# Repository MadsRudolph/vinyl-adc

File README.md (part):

# Vinyl ADC

[Assembly guide & bench log](https://vinyl-adc.madsrudolph.dev/) · [Rev D bring-up, 20 October](docs/bringup-log-2026-10-rev-d.md) · [Bring-up log, 16–18 September](docs/bringup-log-2026-09.md) · [16 September bench plan](assembly/sessions/2026-09-16/README.md) · [6 September test handoff](assembly/sessions/2026-09-06/README.md)

**Rev D (20 October): built, made by PCBWay, and running.** The converter now lives on one four-layer Raspberry Pi HAT, [fabricated by PCBWay](#rev-d-the-pcbway-board), in place of the four hand-milled boards it was born on. Both channels modulated correctly from the first capture, and with the turntable connected the whole chain records about **8 dB more A-weighted range** than the milled stack did, on the Pi's own 5 V. On the bench, on its own crystal, the left channel measures **78.7 dB dynamic range**, 11 dB past the milled stack's best. Record: [rev D bring-up log](docs/bringup-log-2026-10-rev-d.md).

**The milled stack (September):** all four boards are assembled and bench-screened with the AD3 (16–17 September): power, rev B digital with the on-board crystal Pierce, both channels and the full stack pass, after resoldering a crystal leg and swapping the reference op-amp U2 to an LM358 for output headroom on the charge-pump rail (design-notes §10b′). A Raspberry Pi 4 captures the stream, and a ripper service on it records sides automatically, splits and tags the tracks and hands finished albums to the Jellyfin server; setup in [pi/README.md](pi/README.md) and [server/README.md](server/README.md). No complete-system audio performance is claimed by these assembly tests.

**Rev C (22 September):** with a fab available, the four milled boards are redrawn as [one 4-layer board](hardware/kicad/rev_c/README.md), 170 × 120 mm, all through-hole, with the Raspberry Pi 4 plugged into its underside on its own 40-pin header and the bench fixes (LM358 reference, filtered 5 V inlet, series resistors on the I2S clocks) built in. It passes the same intent gate as the milled boards against the reference sheet; [production files](production/vinyl_adc_rev_c/) and a [bill of materials](docs/bom-rev-c.md) are exported. It was never built: rev D superseded it.

**Rev D (designed 22–25 September):** with PCBWay sponsoring the fabrication, the one-board converter is redrawn as a proper [Raspberry Pi HAT](hardware/kicad/rev_d/README.md) — 140 × 136 mm (its layout redone on 24 September: every passive beside the pin it serves, channel R a copy of channel L), four layers, still every part through-hole from the DTU shop — and given the things the bench asked for: an analog supply island behind its own choke (the DAC reference rail, kept away from the Pi's and the charge pump's switching), a second 74HC244 to stiffen the −5 V pump, a damped MCLK, eight front-edge status LEDs (rail, pump, clock-alive, clip L/R from LM339 window comparators, and three under the Pi's control), shutdown and user buttons, a HAT ID EEPROM, test-point headers with ground pins, and a tonearm ground terminal with a lift network. `tools/check_rev_d.py` proves it is the reference circuit plus exactly those additions; [production files](production/vinyl_adc_rev_d/) and the [bill of materials](docs/bom-rev-d.md) are exported. Design record: [design-notes §12](docs/design-notes.md#12-rev-d-the-converter-as-a-raspberry-pi-hat-22-september-2026).

**Rev E (24 September):** the same circuit in common [surface-mount parts](hardware/kicad/rev_e/README.md) on a 118 × 88 mm four-layer HAT — 0805 C0G/X7R and thin-film parts, SOIC logic and op-amps, SOT-23 transistors, shielded SMD chokes — checked by the same gate as rev D, placed and routed by the same tools, DRC clean. [Production files](production/vinyl_adc_rev_e/) include the pick-and-place file for PCBWay assembly; [bill of materials](docs/bom-rev-e.md); design record [design-notes §13](docs/design-notes.md).

<p align="center">

</p>

<p align="center">
  <strong>A Discrete 3rd-Order Continuous-Time Delta-Sigma Stereo Audio ADC</strong><br>
  Engineered from standard analog op-amps &amp; 74HC CMOS logic — <em>zero dedicated ADC ICs anywhere in the signal chain</em>.<br>
  Now one four-layer Raspberry Pi HAT <strong>made by <a href="https://www.pcbway.com">PCBWay</a></strong>; first built on four boards isolation-milled on a Roland SRM-20 using <a href="https://github.com/MadsRudolph/srm-cam"><strong>SRM-CAM</strong></a>.
</p>

<p align="center">
  <a href="media/showcase/README.md">Download GIF animations &amp; print files</a>
</p>

<details>
<summary><strong>More views: the enclosure orbit and exploded assembly</strong></summary>

### Product orbit

### Exploded assembly

</details>

<p align="center">
  👉 <strong><a href="https://madsrudolph.github.io/vinyl-adc/">Launch Live Interactive 3D Web Viewer &amp; Explosion Slider</a></strong> 👈
</p>

---

## Rev D: the PCBWay board

**One board, four layers, made by [PCBWay](https://www.pcbway.com), and the best-measuring version of this converter so far.**

Every Vinyl ADC board before rev D was isolation-milled, single-sided, at the university workshop. When **PCBWay offered to sponsor the fabrication**, the converter could finally be drawn the way a mixed-signal circuit wants to be: one board, a solid ground plane, plated holes everywhere, and the Raspberry Pi plugged in underneath. Thank you to PCBWay for making that possible; this section is about what their boards did for the project.

<p align="center">
  <br>
  <sub>Before and after: the four-board milled stack, and rev D as PCBWay made it.</sub>
</p>

<p align="center">
  
  <br>
  <sub>The bare board as it arrived, both sides.</sub>
</p>

### What PCBWay made

| | Rev D, per board |
|---|---|
| Stack-up | **4 layers**: signals / solid GND plane / split +5V·+5VA / signals, 1.6 mm FR-4, 1 oz copper |
| Finish | green solder mask on both sides, white silkscreen, HASL lead-free |
| Holes | **636 plated through-holes and 13 vias**: 649 plated barrels on every board, five boards |
| Routing | 1,020 tracks, the narrowest 0.25 mm; drills from 0.4 mm to 2.7 mm |
| Legends | 184 reference designators at 1 mm text height, the smallest labels 0.8 mm |
| Parts | 184, every one through-hole, socketed ICs |
| Size | 140 × 136 mm, a Raspberry Pi 4 HAT |

<p align="center">
  
  <br>
  <sub>Up close: legends under a millimetre tall come out clean, and every barrel is plated and tinned.</sub>
</p>

### Ordering and what arrived

These are the first professionally made boards I have ever had, so I was very excited to get my hands on them. The order went in through PCBWay's normal online flow on 25 September, from the Gerbers with the copper layer order in the remarks, and their engineers had no questions for me. That was shortly before China's National Day holiday, so things took a little longer, which is understandable and no problem at all. The boards were built up and running on my bench by 20 October.

The package felt premium: the boards were vacuum-sealed in bubble wrap and cushioned by soft styrofoam, which made unpacking them a pleasure. I found no issues with their quality. Assembling them, every footprint matched its part exactly, the clear silkscreen made placing the components easy, and the pre-tinned HASL pads were very nice to hand-solder.

I have built one board so far, since one is all the project needs, so the others are untested spares. On the one I built, no fault has traced back to the fab.

### Why a fab board, for a converter

- **A real ground plane.** A delta-sigma modulator switches at 1.536 MHz next to integrators that resolve microvolts. On one milled layer, ground was whatever copper was left between tracks. On rev D an entire inner layer is ground, directly under every signal, and a large part of the improvement measured below is owed to it.
- **Plated holes.** Every joint is soldered from one side and the barrel carries it through. The single most expensive fault of the September bring-up, a −5 V rail that reached one board only through solder wicked up an unplated hole, cannot exist on this board.
- **Repeatability.** Five identical boards. The milled boards were each a one-off; a second rev D is the same board as the first.

### Milled against fabricated

| | Milled stack (Sept 2026) | Rev D by PCBWay (Oct 2026) |
|---|---|---|
| Boards | 4 × 100 × 100 mm, stacked on a bus | **1 × 140 × 136 mm** Raspberry Pi HAT |
| Copper | 1 layer, milled, bare copper | **4 layers** with a solid ground plane |
| Links | dozens of wire jumpers | **none**: plated through-holes and vias |
| Finish | none | solder mask both sides, silkscreen, HASL lead-free |
| Supply for best figures | bench supply (the Pi's 5 V cost 6–11 dB) | **the Pi's 5 V**, analog island behind its own choke |
| Bring-up | two days, two hidden faults in one channel | **both channels healthy and matched at the first capture** |

**Measured, with the turntable connected** (stylus up, same phono stage, same method, music peaks set to −6 dBFS on both builds):

| 20 Hz–20 kHz | Milled stack, bench supply, crystal clock | **Rev D, Pi 5 V, Pi clock** (crystal not yet running) |
|---|---|---|
| Idle floor, A-weighted | −61.1 / −62.1 dBFS | **−69.7 / −68.2 dBFS** |
| Idle floor, 200 Hz–2 kHz | −68.6 / −69.4 dBFS | **−73.7 / −73.6 dBFS** |
| Idle floor, 2–20 kHz | −59.6 / −60.6 dBFS | **−76.5 / −70.5 dBFS** |
| Music peak to floor, A-weighted | 54.2 / 55.2 dB | **63.7 / 62.2 dB** |
| Music peak to floor, unweighted | 48.9 / 49.2 dB | **51.4 / 51.3 dB** |

### What that adds up to

About **8 dB more A-weighted range** from the groove to the file, and a noise floor 5–17 dB lower everywhere above 200 Hz, measured on the Raspberry Pi's 5 V (the supply that cost the milled stack the most) and, at the time, on the Pi's own clock. What remains in the unweighted figure is 50 Hz hum common to both channels: the turntable's grounding, not the converter.

**On the bench, with its own crystal** (AD3 generator into the input, other input shorted, Pi supply):

| | Milled stack, best channel | **Rev D, left** | Rev D, right |
|---|---|---|---|
| Dynamic range (AES17, A-weighted) | 67.9 dB | **78.7 dB** | 72.2 dB |
| THD at −6 dBFS | 0.03 % | **0.019 %** | 0.052 % |
| Crosstalk | −92.4 dB | **−97.8 dB** | −85.8 dB |
| Response 20 Hz–16 kHz | ±0.06 dB | −0.30 / +0.08 dB | −0.33 / +0.08 dB |

The left channel is **about 11 dB better than anything the milled boards achieved**, and 10 dB past the ~68 dB the design was simulated for. The right channel carries an extra in-band floor that the milled stack's right channel had too; it is traced to the right modulator's own loop and still being chased ([bring-up log §10](docs/bringup-log-2026-10-rev-d.md#10-the-right-channels-deficit-is-in-its-loop-and-it-is-not-new)).

Bring-up said as much as the measurements. The milled stack took two days and two faults that hid each other before its right channel modulated. On rev D both channels were healthy, and matched, on the first capture. The one rev D fault found so far is my own design error, not the fab's: the clip-LED comparators' inputs are swapped in the schematic, documented as an [erratum](docs/bringup-log-2026-10-rev-d.md#7-erratum-the-clip-leds-are-lit-all-the-time) with a rework that stays on the underside.

<p align="center">
  <br>
  <sub>Assembled and running on its Raspberry Pi 4.</sub>
</p>

<p align="center">
  <br>
  <sub>CAD renders (<a href="media/showcase/rev-d/README.md">all views and how they are made</a>); Raspberry Pi 4 model from the FreeCAD parts library, CC BY 3.0.</sub>
</p>

The [Gerbers and production files](production/vinyl_adc_rev_d/), the [KiCad project](hardware/kicad/rev_d/README.md) and the [full rev D bring-up log](docs/bringup-log-2026-10-rev-d.md) are all in this repo. Boards sponsored by **[PCBWay](https://www.pcbway.com)**: thank you for making the project's best version possible.

---

## Audiophile Engineering Specifications

| Specification | Target / Measured Performance | Design Rationale & Implementation |
|---|---|---|
| **Modulator Topology** | Continuous-Time CIFB (Cascade of Integrators, Feedback) | 3rd-order active RC loop with local resonator feedback (`G = 0.03`) |
| **Dynamic Range / SNR** | **Rev D: 78.7 dB left, 72.2 dB right** (AES17, A-weighted). Milled stack: 67.9 dB, best channel | Purposefully matched to the physical vinyl surface noise floor (~60–65 dB) |
| **Audio Output** | **24-bit / 48 kHz Linear PCM FLAC** | Decimated in software on Raspberry Pi CPU (CIC filter + compensation FIR) |
| **Modulator Sampling Rate ($F_s$)** | **1.536 MHz** ($32\times$ OverSampling Ratio) | Matches bandwidth constraints of DTU-stocked op-amps (`TL072` 3 MHz GBW) |
| **Master Clock ($F_{clk}$)** | **6.144 MHz crystal Pierce oscillator** (74HCU04 + HC-49 crystal) | Direct low-jitter clock ($<50\text{ ps}$ jitter vs. Pi PLL phase noise); also available as a plug-in module for the rev A board |
| **Digital Stream Format** | Bit-Interleaved PDM on standard I2S bus | 3.072 Mbps data stream, read as 32-bit stereo audio frames at 48 kHz |
| **Analog Inputs** | Gold RCA Phono Jacks &amp; 5.08 mm Screw Terminals | Switchable input gain via front-panel multi-turn trim potentiometer |
| **Analog Grounding** | Star-ground topology with tonearm binding post | Eliminates 50 Hz turntable motor hum and ground-loop switching transients |
| **PCB Manufacturing** | Rev D: 4-layer 1.6 mm FR-4, HASL lead-free, by **[PCBWay](https://www.pcbway.com)**. First build: isolation-milled single-sided FR4 | Milled toolpaths generated via [**SRM-CAM**](https://github.com/MadsRudolph/srm-cam) on a **Roland SRM-20** mill |
| **Enclosure Dimensions** | $144.0\text{ mm} \times 144.0\text{ mm} \times 105.0\text{ mm}$ | Open organic lattice, reinforced connector islands and M3 lid inserts; recessed $3.0\text{ mm}$ acrylic lid |

---

## Printable enclosure

The enclosure has an open, rounded lattice on all four sides and 40 mm more height for the PCB stack and cable routing. Solid connector islands and reinforced lid-insert bosses carry the mounting loads. **Print upright with supports**; the revised mesh and supported slice pass validation, but physical print/fit testing is still pending.

[STL, 3MF, insert-fit coupon and printing instructions](enclosure/README.md) · [Three looping GIFs](media/showcase/README.md)

## Signal Processing Flow

```
   ┌─────────────────────────────────────────────────────────────────────────────┐
   │                          ANALOG SIGNAL CHAIN (HARDWARE)                     │
   │                                                                             │
   │  Turntable (Debut Carbon)                                                  │
   │         │                                                                   │
   │         ▼                                                                   │
   │  Phono Preamplifier                                                         │
   │         │                                                                   │
   │         ▼                                                                   │
   │  [ VINYL ADC ] ──> 3rd-Order CT-ΔΣ ──> 1.536 MHz PDM ──> 74HC157 Mux       │
   │   Gold RCA In      TL072 + LM311       74HC74 Retimed    Stereo Interleave  │
   └─────────────────────────────────────────────────────────────────┬───────────┘
                                                                     │ 3.072 Mbps
                                                                     ▼
   ┌─────────────────────────────────────────────────────────────────────────────┐
   │                         DIGITAL DSP CHAIN (RASPBERRY PI)                    │
   │                                                                             │
   │  ALSA I2S Interface (48 kHz / 32-bit Frame Capture)                         │
   │         │                                                                   │
   │         ▼                                                                   │
   │  Software De-interleaver (Separates Left & Right Bitstreams)                │
   │         │                                                                   │
   │         ▼                                                                   │
   │  4th-Order CIC Decimator (Downsamples 32x to 48 kHz Nyquist)                │
   │         │                                                                   │
   │         ▼                                                                   │
   │  FIR Droop & Phase Compensation Filter                                      │
   │         │                                                                   │
   │         ▼                                                                   │
   │  24-bit / 48 kHz Bit-Perfect FLAC Encoder ──> Jellyfin Media Server         │
   └─────────────────────────────────────────────────────────────────────────────┘
```

---

## Noise-Shaping & SPICE Verification

The defining characteristic of delta-sigma conversion is **noise shaping**: pushing quantization noise out of the audible spectrum into ultrasonic frequencies where digital decimation filters remove it completely.

- **Time-Domain (Top):** Shows the incoming 1 kHz analog test sine wave alongside the discrete 1.536 MHz 1-bit decision stream. The pulse density cleanly mirrors the instantaneous input amplitude.
- **Frequency-Domain (Bottom):** Measured FFT spectrum with Hann windowing. The audible passband (20 Hz – 20 kHz, shaded green) exhibits a **68.3 dB SNR** with clean third-order $+60\text{ dB/decade}$ noise shaping that drives quantization noise above 30 kHz.

---

## The original 4-board milled stack (rev A/B)

To overcome the routing limitations of single-layer CNC isolation milling (0.84 mm clearance between DIP pins), the system is split into four 100 × 100 mm boards interconnected by a 16-pin ribbon bus and M3 brass standoffs:

| Tier & Board | 3D Raytraced Board Render | Function & Key Components |
|---|:---:|---|
| **Tier 4 (Top)**<br>[`vinyl_adc_digital`](hardware/kicad/digital/) |  | **Clock, Interleaving & Pi Interface:**<br>• 6.144 MHz crystal Pierce oscillator (`Y1` + `74HCU04`)<br>• `74HCT132` Schmitt-trigger clock buffer<br>• `74HC4040` binary clock divider ($F_s = 1.536\text{ MHz}$, $\text{BCLK} = 3.072\text{ MHz}$, $\text{LRCLK} = 48\text{ kHz}$)<br>• `74HC157` stereo bit-interleaving MUX<br>• `74HC4049` 5 V $\rightarrow$ 3.3 V level shifter to Raspberry Pi |
| **Tier 3**<br>[`vinyl_adc_channel_l`](hardware/kicad/channel_l/) |  | **Left Channel Modulator:**<br>• 3rd-order active RC integrators (`TL072`)<br>• `LM311` high-speed comparator<br>• `74HC74` retiming flip-flop &amp; 1-bit DAC network<br>• Multi-turn input gain trim potentiometer<br>• Jumper set to Left (`pins 1-2`) |
| **Tier 2**<br>[`vinyl_adc_channel_r`](hardware/kicad/channel_r/) |  | **Right Channel Modulator:**<br>• Identical artwork to Tier 3 (milled twice)<br>• Jumper set to Right (`pins 2-3`)<br>• Independent ground plane &amp; analog reference |
| **Tier 1 (Base)**<br>[`vinyl_adc_power`](hardware/kicad/power/) |  | **Power & Reference Generation:**<br>• `74HC244` + `1N5817` charge-pump negative rail<br>• Low-noise precision virtual ground reference (`TL072`)<br>• High-capacity bulk reservoir &amp; post-filter network<br>• 4× M3 mounting holes seated onto enclosure floor bosses |

---

## PCB Fabrication with SRM-CAM & Roland SRM-20

The four boards of the first build were designed for single-sided isolation milling on the **Roland SRM-20** desktop CNC mill at the DTU FabLab. That constraint is why the converter was split into four boards with dozens of wire links; [rev D](#rev-d-the-pcbway-board) is the same circuit on a fabricated four-layer board.

<p align="center">
  
</p>

The RML-1 milling toolpaths and G-code were generated directly using [**SRM-CAM**](https://github.com/MadsRudolph/srm-cam) (`gerber2rml`):
- **Isolation Routing:** Traces isolation-milled on `B.Cu` using 0.2 mm / 0.4 mm V-bits with wide rubout for ground separation.
- **Excellon Drilling:** Automatic hole-center extraction from KiCad `*.drl` files for all DIP sockets, film caps, resistors, and headers.
- **Edge Routing:** Clean board profiling with 1.0 mm end mill for the 100 × 100 mm PCB footprint and M3 mounting holes.
- **Workpiece Fixturing:** Copper-clad FR4 secured using the double-sided tape &amp; CA glue method documented in the [SRM-CAM User Guide: Holding the copper](https://madsrudolph.github.io/srm-cam/holding-the-copper.html).

All production Gerbers and Excellon drill files ready for SRM-CAM are located in [`production/`](production/).

---

## Raspberry Pi Wiring & Star-Grounding Architecture

Turntable systems are exceptionally sensitive to 50/60 Hz hum and digital switching noise. The Vinyl ADC implements an isolated star-grounding architecture:

```mermaid
graph TD
    subgraph Analog Front-End
        TT["Turntable Ground Spade"] --- Post["Chassis Ground Binding Post"]
        RCA["RCA Input Outer Shield"] --- Post
        Post --- Star(("★ STAR GROUND"))
        Star --- Tier1["Tier 1 Analog Virtual Ground"]
    end

    subgraph Raspberry Pi Connection
        Star -.->|Isolated Digital Return| Pi_GND["Pin 6 / 9 (GND)"]
        Tier4["Tier 4 Logic Bus"] -->|Pin 12 / GPIO 18| Pi_BCLK["PCM_CLK (3.072 MHz)"]
        Tier4 -->|Pin 35 / GPIO 19| Pi_LRCLK["PCM_FS (48 kHz)"]
        Tier4 -->|Pin 38 / GPIO 20| Pi_DIN["PCM_DIN (3.072 Mbps)"]
        Pi_Power["Pin 2 / 4 (+5V)"] -->|Filtered DC Rail| Tier1_Pwr["Tier 1 Power In"]
    end
```

### Raspberry Pi 40-Pin GPIO Pinout:

This is the milled stack's wiring. Rev D plugs onto the Pi as a HAT and also uses GPIO3/4/17/22/23/27 and the ID EEPROM pins: see [pi/README.md §7](pi/README.md#7-rev-d-hat-what-the-board-puts-on-the-gpio-header).

| Raspberry Pi Pin | Signal Name | Vinyl ADC Connection | Function |
|---|---|---|---|
| **Pin 2 or 4** | `+5V Power` | Tier 1 DC Input | Supplies digital and analog converter power |
| **Pin 6 or 9** | `GND` | Tier 4 Logic Ground | Digital switching current return |
| **Pin 12 (GPIO 18)** | `PCM_CLK` | Tier 4 Clock Out | 3.072 MHz bit clock for I2S capture |
| **Pin 35 (GPIO 19)** | `PCM_FS` | Tier 4 Frame Sync | 48 kHz word clock (L/R frame framing) |
| **Pin 38 (GPIO 20)** | `PCM_DIN` | Tier 4 Interleaved PDM | Serial stream carrying alternating Left/Right bits |

---

## Repository Structure

```
├── docs/                           # Documentation & Interactive Web App
│   ├── index.html                 # Interactive 3D Web Viewer for GitHub Pages
│   ├── vinyl_adc_assembled.glb    # Complete 3D CAD model with explosion timeline
│   ├── shopping-list.md           # Component shop procurement list
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
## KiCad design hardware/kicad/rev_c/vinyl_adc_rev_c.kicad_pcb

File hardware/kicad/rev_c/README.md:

# Rev C: the whole converter on one fabricated 4-layer board

The four CNC-milled boards exist because of one number: 0.84 mm between two
DIP pads, which nothing could pass on the single-sided mill (see
`../PCB-NOTES.md`). A fab removes that constraint, and with it the reason to
split, so rev C is the reference sheet built as it was drawn -- one board,
170 x 120 mm, four layers, every part through-hole and socketed exactly as
before, with the Raspberry Pi 4 plugged into the underside on its own 40-pin
header. The measured rev B stack (docs/bringup-log-2026-09.md 13a) is the
baseline this board will be compared against.

## What changed against the reference sheet, and nothing else

`tools/check_rev_c.py` welds three two-pin parts through, drops the Pi
connector on both sides, and requires the remaining node partition to be
identical to `../reference/vinyl_adc.kicad_sch`. It passes with 99 nets each
side. The three parts, and the fourth change it cannot see:

| Change | Why | Where it came from |
|---|---|---|
| U2 is an LM358, not a TL072 | VREF_N must reach -2.5 V from a pump rail that sags to -3.8 V; a TL07x stops 2 V above V- | bench 16 Sept, design-notes 10b' |
| FB1 ferrite bead on the 5 V inlet | the board is now powered from the Pi's 5 V pins and the Pi's switching noise was measurably worse than the bench supply | bringup log, open item 4 |
| R12, R13 = 475 R in BCLK and LRCLK | the Pi's I2S pins are outputs until a stream is opened, so two drivers meet on those lines at boot | bringup log 6.3 |
| J2 is the Pi's 2x20 header | no pigtail, no stacking bus, one box | this revision |

Everything else -- the modulator, the quantiser, the clock tree, the
values, the Pierce oscillator from rev B -- is the same drawing, called from
the same block functions in `../tools/vinyl_adc_layout.py` (`board_rev_c`).

## Stackup and rules

`F.Cu` signals, `In1.Cu` solid GND, `In2.Cu` solid +5V, `B.Cu` signals.
Through-hole pads reach both planes on their own, so GND and +5V need no
tracks at all: the router only ever sees the 66 other nets. Tracks 0.3 mm,
supplies (-5V, +3V3, PUMP, VREF_P, VREF_N) 0.6 mm, clearance 0.2 mm, vias
0.7/0.35 mm -- twice PCBWay's 4-layer minimums throughout. Thermal reliefs
on the planes, because every lead is hand-soldered and a lead into a solid
inner plane sinks the iron.

## Floorplan

```
  x 0..112                              x 114..170
  y   4..56   CHANNEL L  J20 RV20 -> U20 U22 U21 / U23 U24     DIGITAL  Y1 U9 J1
                                                                         U3 U4
  y  60..112  CHANNEL R  J60 RV60 -> U60 U62 U61 / U63 U64              U6 U8
                                                               inlet     FB1 C1 C2
                                                               POWER     U1 C4 D1 D2
                                                                         U2 R2-R5 C5 R1 C6
```

Each channel reads left to right like its schematic band; the integrator
resistor clusters sit between the packages they feed, the DAC gates and the
retiming flip-flop below, next to the summing resistors they drive. The
digital column is beside the Pi socket so MCLK, the I2S trio and the level
shifter are short, and the power section is at the far end of the board from
the inputs. `tools/rev_c_board.py` holds the numbers.

## The Pi, and the one fact about it worth writing down

The Pi sits UNDER the board, HAT-style, on a 2x20 female header soldered to
the copper side at (117.5, 32.5); its four holes are at (117.5, 3.5),
(166.5, 3.5), (117.5, 61.5), (166.5, 61.5). Its USB-C/HDMI edge is flush
with the board's right edge and its USB/Ethernet end overhangs the TOP edge
by 20 mm -- the same 65 mm reach the HAT specification uses, because those
connectors stand 16 mm proud and would hit the board.

Handedness: seen from above, pin 1 (3V3) is the row NEARER the Pi's centre,
pin 2 (5V) the row along the Pi's edge, both at the SD-card end. The first
attempt put the Pi's SD end at the bottom and its header edge on the left,
which reads naturally and is a mirror image -- no rotation of a back-side
socket could land pins 1, 2 and 39 on it. `place_pi_socket()` searches the
four rotations and refuses the placement rather than guessing, which is what
caught it. Verified against KiCad's own `Raspberry_Pi_Zero_Socketed`
footprint: header centre on the hole line, holes 29 mm either side.

The Pi's PoE header (8.5 mm, near its Ethernet jack) lands under about
(117-122, 4-8), which is exactly the top end of the socket; nothing else is
there. A plain 8.5 mm HAT socket touches it; an 11 mm extended-height socket
does not. Use the taller one if in doubt.

The Pi powers the board: 73 mA at 5 V through FB1 (bringup log 13). The
board is the I2S master, as before.

## Regenerating it

```bash
cd hardware/kicad
PYTHONPATH=<dir holding the pcbnew sitecustomize shim> REV_C_SCRATCH=/tmp/rev_c \
    tools/rev_c_pipeline.sh
```

That runs, in order: `vinyl_adc_layout.py vinyl_adc_rev_c` (the sheet),
`kicad-cli sch export netlist`, `check_rev_c.py` (the gate),
`pcb_netlist_json.py` (from the kicad-laser-pcb skill), `rev_c_board.py`
(placement, planes, rules), `route_rev_c.py` (FreeRouting on four layers,
retried with different via and direction costs until DRC shows zero
unconnected), `export_rev_c.sh` (Gerbers, drills, PDFs, renders into
`production/vinyl_adc_rev_c/`) and `make_bom.py rev_c` (`docs/bom-rev-c.md`).

Two things about the router. FreeRouting 1.9.0 has no headless mode and
2.3.0 needs Java 25; on Hyprland the script installs a session-only window
rule (`hyprctl eval 'hl.window_rule(...)'`) that sends its window to a
silent special workspace, and reads `hyprctl clients` afterwards to confirm
it went there. And it is deterministic for identical input: a run that
leaves a net open is not retried with the same costs but with the next pair
in the list. On this board the first two pairs left VREF_P open by one
segment; the third (against 2.5, via 40) closed everything with 3 vias.

## Where it stands (22 September 2026)

| | |
|---|---|
| parts | 111 + 8 mounting holes, all through-hole, every IC socketed |
| nets | 68 on the board (99 on the sheet before the planes swallow GND and +5V and the Pi's NC pins) |
| copper | F.Cu 1597 mm, B.Cu 1955 mm, 3 vias, GND and +5V as planes |
| gates | ERC clean (42 lib-symbol-mismatch warnings, same as every sheet here); `check_rev_c.py` OK; `sch_score` passes except the 55 deliberately NC pins it counts as floating; DRC 0 unconnected, 2 silk-over-copper warnings (references clipped by the mask, cosmetic) |
| production | `production/vinyl_adc_rev_c/`, see its README for the order parameters |

Not done: the enclosure. `enclosure/build_enclosure.py` models the
100 x 100 mm stack and must be rebuilt for a 170 x 120 board with the Pi
underneath and 20 mm of Pi beyond the top edge. Not done either: building
and measuring it, which is the point of the exercise -- the milled stack's
67.9 dB dynamic range is the number to beat, and whether a ground plane
moves it is the question.

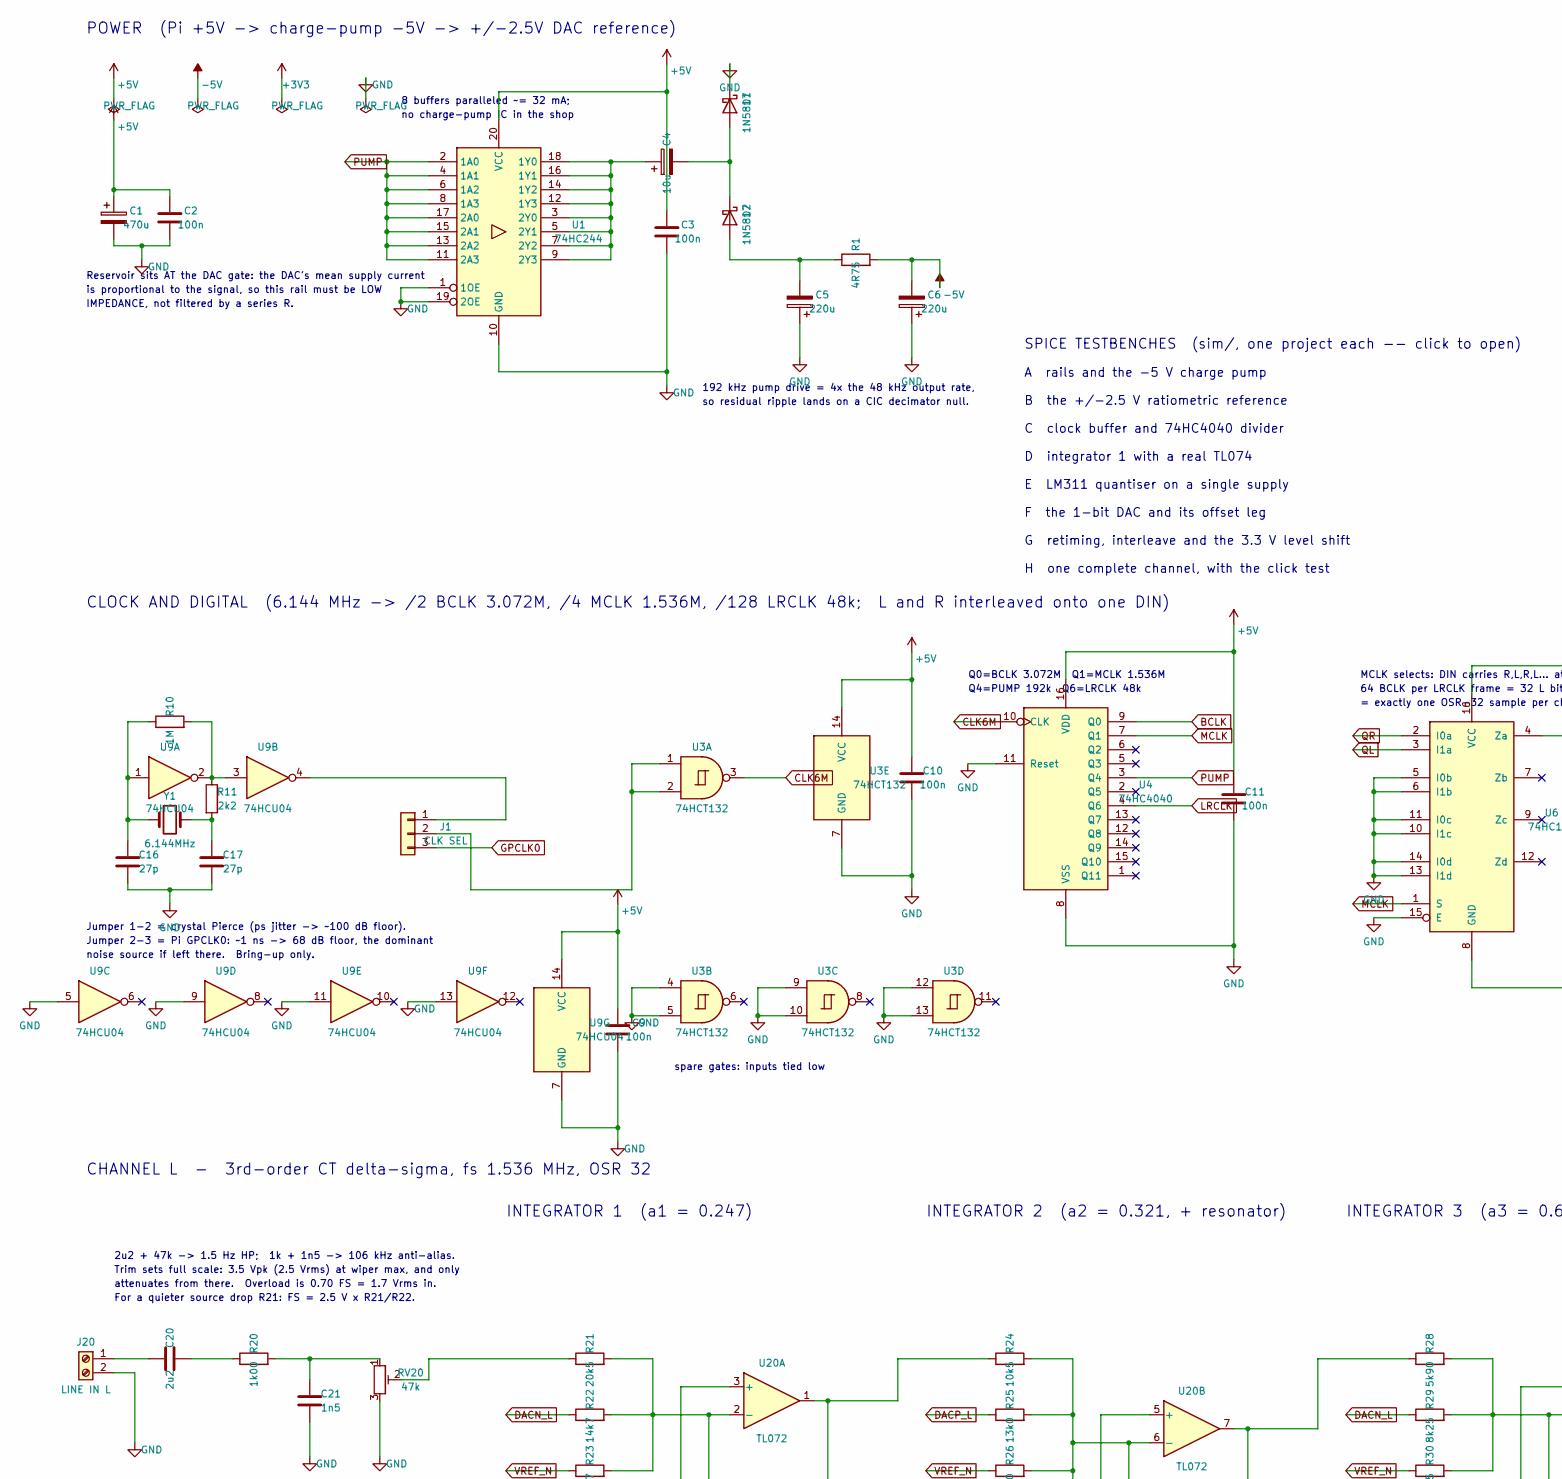
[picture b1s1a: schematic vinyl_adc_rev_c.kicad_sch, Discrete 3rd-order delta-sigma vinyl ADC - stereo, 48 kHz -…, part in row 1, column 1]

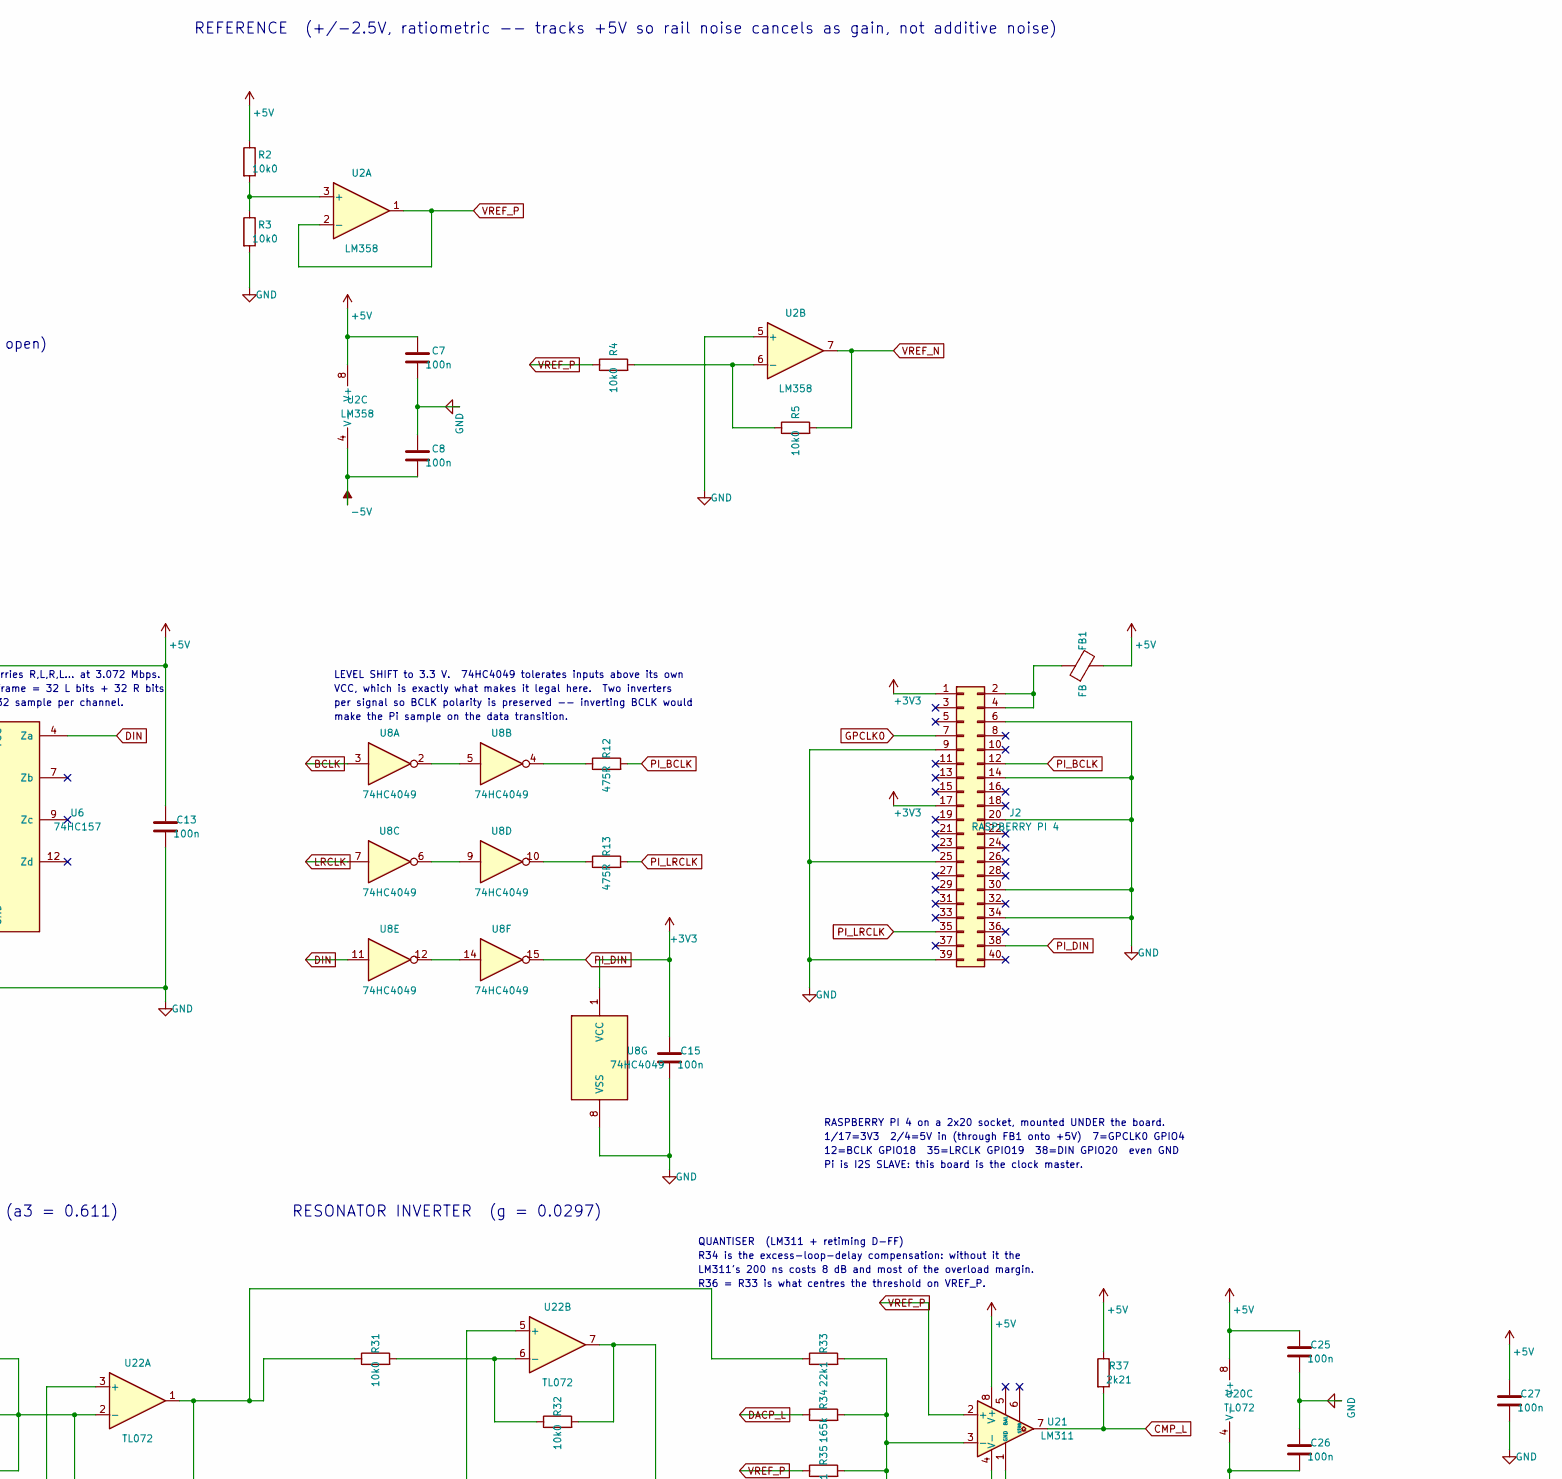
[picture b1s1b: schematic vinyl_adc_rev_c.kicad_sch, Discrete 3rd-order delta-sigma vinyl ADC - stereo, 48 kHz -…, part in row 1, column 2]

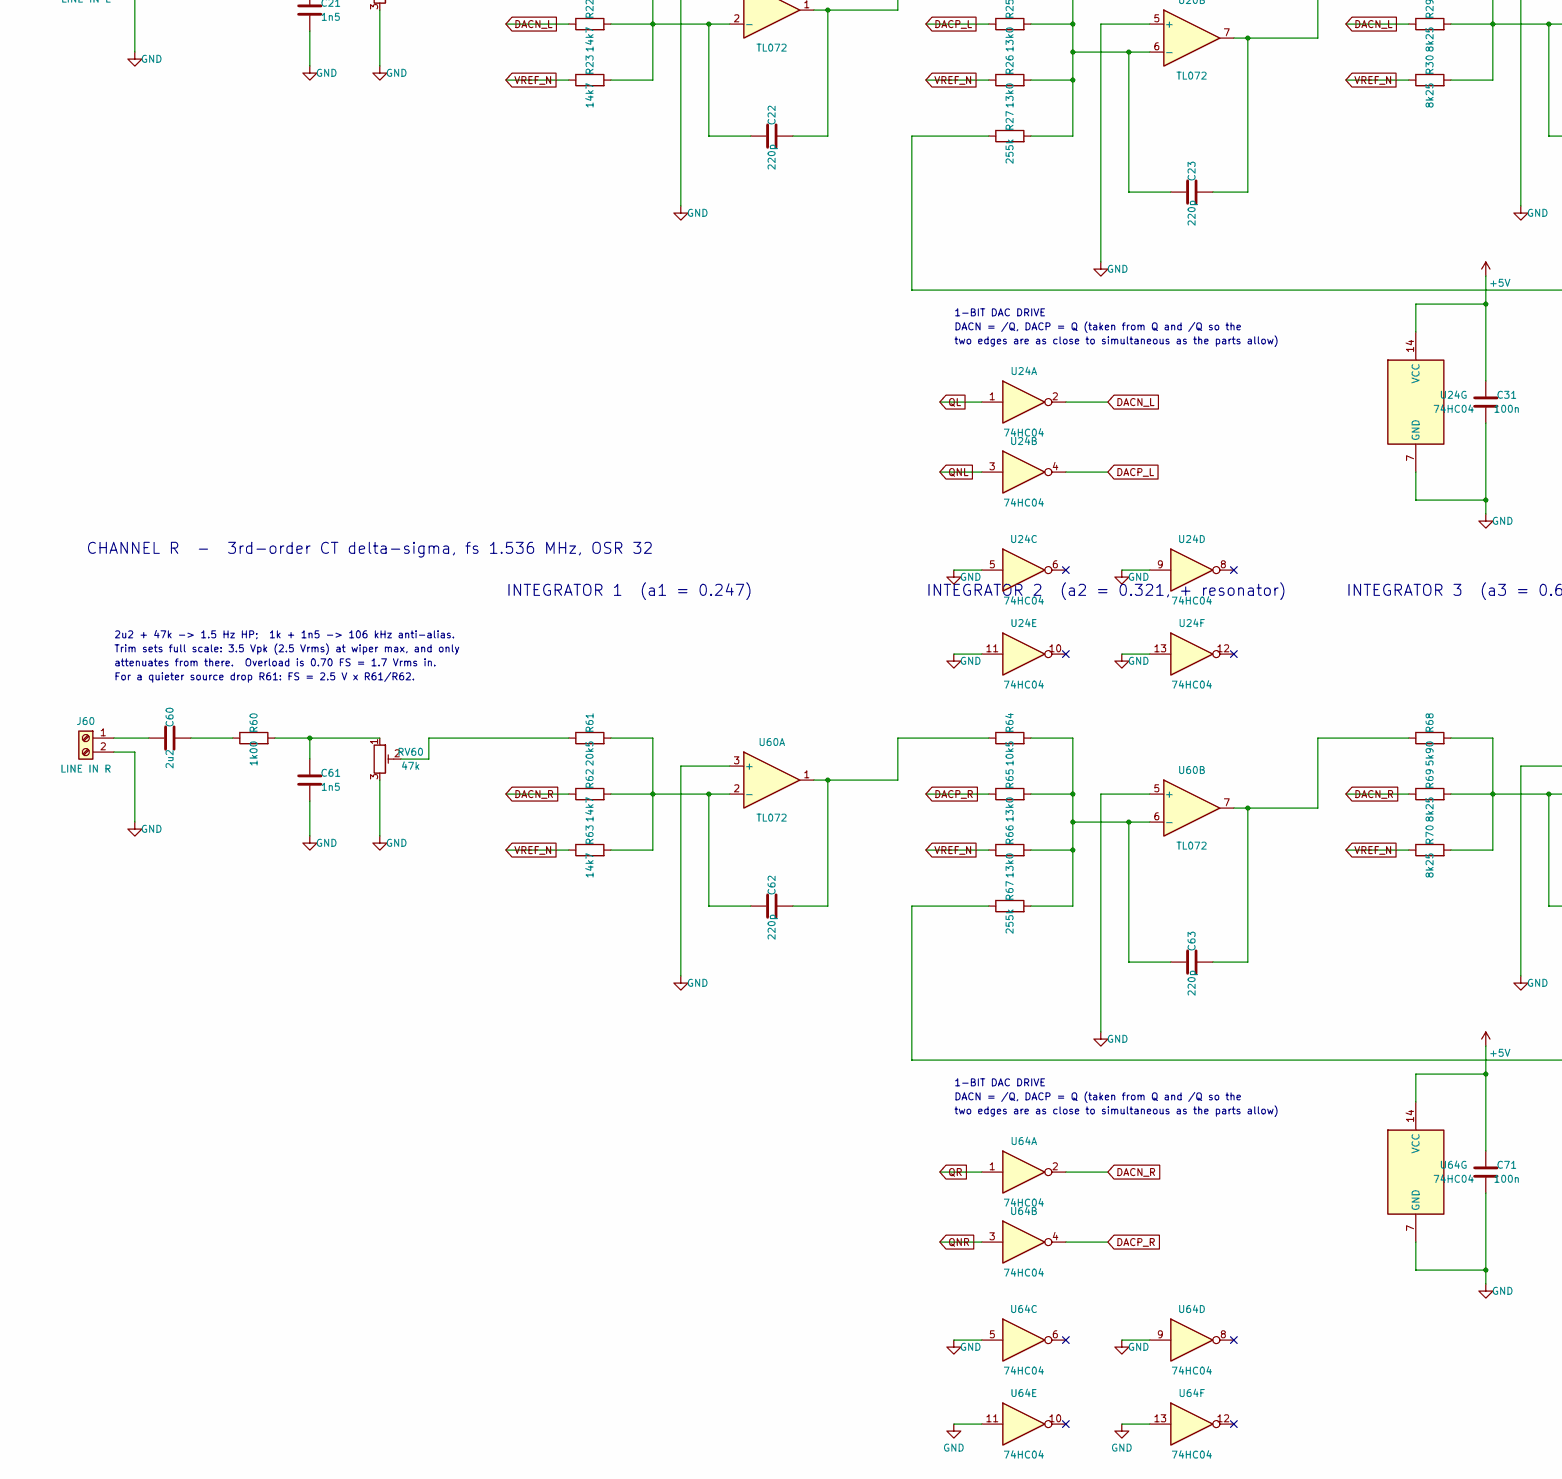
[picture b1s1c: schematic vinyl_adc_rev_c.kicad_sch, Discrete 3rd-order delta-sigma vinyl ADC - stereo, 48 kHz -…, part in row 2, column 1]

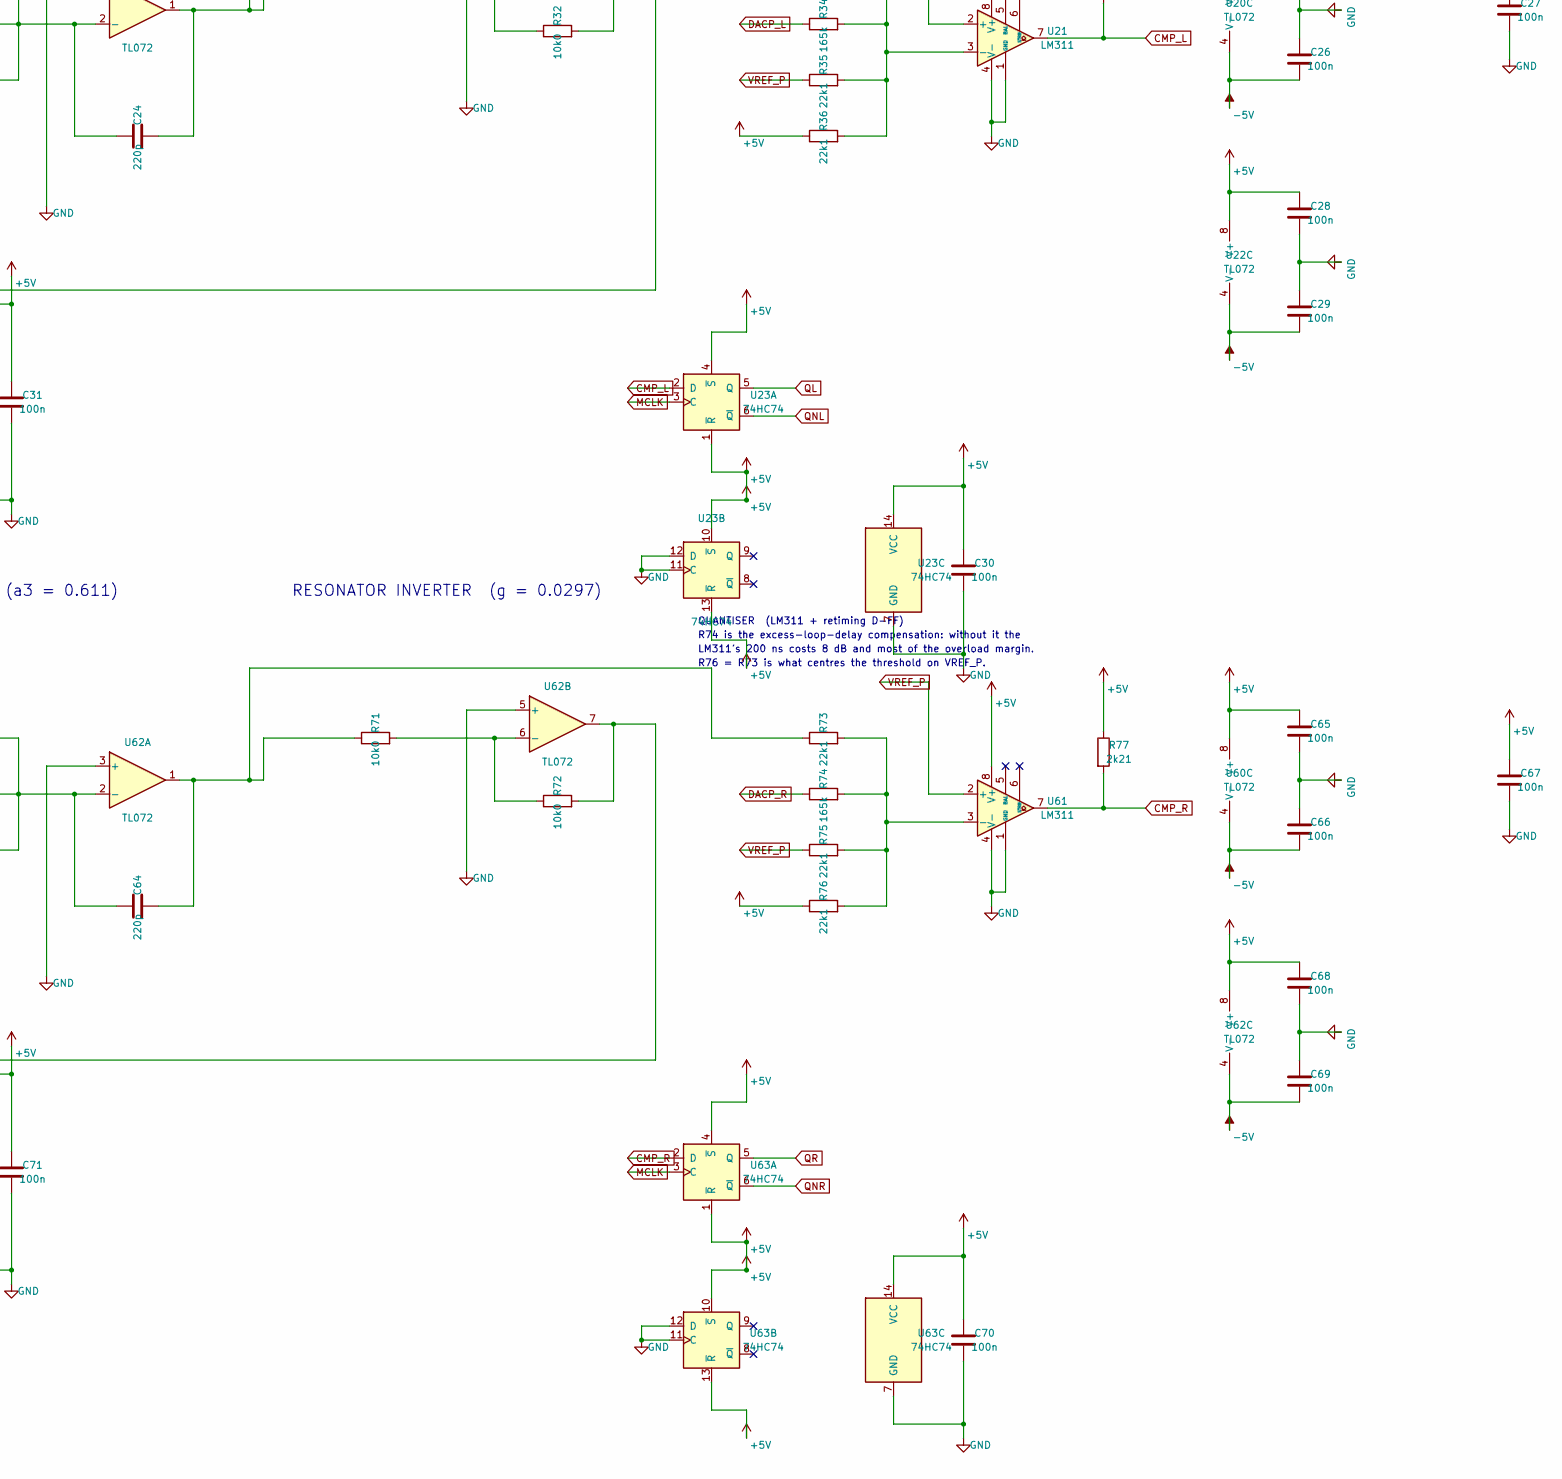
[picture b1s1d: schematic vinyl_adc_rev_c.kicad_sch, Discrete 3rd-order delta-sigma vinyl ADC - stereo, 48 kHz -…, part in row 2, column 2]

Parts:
C1: 470u; CP_Radial_D10.0mm_P5.00mm
C2, C3, C7, C8, C9, C10, C11, C13, C15, C25, C26, C27, C28, C29, C30, C31, C65, C66, C67, C68, C69, C70, C71: 100n; C_Disc_D5.0mm_W2.5mm_P5.00mm
C4: 10u; CP_Radial_D8.0mm_P3.50mm
C5, C6: 220u; CP_Radial_D8.0mm_P3.50mm
C16, C17: 27p; C_Disc_D5.0mm_W2.5mm_P5.00mm
C20, C60: 2u2; C_Rect_L11.0mm_W6.3mm_P10.00mm_MKT
C21, C61: 1n5; C_Disc_D5.0mm_W2.5mm_P5.00mm
C22, C23, C24, C62, C63, C64: 220p; C_Disc_D5.0mm_W2.5mm_P5.00mm
D1, D2: 1N5817; D_DO-41_SOD81_P10.16mm_Horizontal
FB1: FB; L_Axial_L7.0mm_D3.3mm_P10.16mm_Horizontal_Fastron_MICC
J1: CLK SEL; PinHeader_1x03_P2.54mm_Vertical
J2: RASPBERRY PI 4; PinSocket_2x20_P2.54mm_Vertical
J20: LINE IN L; TerminalBlock_bornier-2_P5.08mm
J60: LINE IN R; TerminalBlock_bornier-2_P5.08mm
R1: 4R75; R_Axial_DIN0207_L6.3mm_D2.5mm_P7.62mm_Horizontal
R2, R3, R4, R5, R31, R32, R71, R72: 10k0; R_Axial_DIN0207_L6.3mm_D2.5mm_P7.62mm_Horizontal
R10: 1M; R_Axial_DIN0207_L6.3mm_D2.5mm_P7.62mm_Horizontal
R11: 2k2; R_Axial_DIN0207_L6.3mm_D2.5mm_P7.62mm_Horizontal
R12, R13: 475R; R_Axial_DIN0207_L6.3mm_D2.5mm_P7.62mm_Horizontal
R20, R60: 1k00; R_Axial_DIN0207_L6.3mm_D2.5mm_P7.62mm_Horizontal
R21, R61: 20k5; R_Axial_DIN0207_L6.3mm_D2.5mm_P7.62mm_Horizontal
R22, R23, R62, R63: 14k7; R_Axial_DIN0207_L6.3mm_D2.5mm_P7.62mm_Horizontal
R24, R64: 10k5; R_Axial_DIN0207_L6.3mm_D2.5mm_P7.62mm_Horizontal
R25, R26, R65, R66: 13k0; R_Axial_DIN0207_L6.3mm_D2.5mm_P7.62mm_Horizontal
R27, R67: 255k; R_Axial_DIN0207_L6.3mm_D2.5mm_P7.62mm_Horizontal
R28, R68: 5k90; R_Axial_DIN0207_L6.3mm_D2.5mm_P7.62mm_Horizontal
R29, R30, R69, R70: 8k25; R_Axial_DIN0207_L6.3mm_D2.5mm_P7.62mm_Horizontal
R33, R35, R36, R73, R75, R76: 22k1; R_Axial_DIN0207_L6.3mm_D2.5mm_P7.62mm_Horizontal
R34, R74: 165k; R_Axial_DIN0207_L6.3mm_D2.5mm_P7.62mm_Horizontal
R37, R77: 2k21; R_Axial_DIN0207_L6.3mm_D2.5mm_P7.62mm_Horizontal
RV20, RV60: 47k; PinHeader_1x03_P2.54mm_Horizontal
U1: 74HC244; DIP-20_W7.62mm_LongPads
U2: LM358; DIP-8_W7.62mm_LongPads
U3: 74HCT132; DIP-14_W7.62mm_LongPads
U4: 74HC4040; DIP-16_W7.62mm_LongPads
U6: 74HC157; DIP-16_W7.62mm_LongPads
U8: 74HC4049; DIP-16_W7.62mm_LongPads
U9: 74HCU04; DIP-14_W7.62mm_LongPads
U20, U22, U60, U62: TL072; DIP-8_W7.62mm_LongPads
U21, U61: LM311; DIP-8_W7.62mm_LongPads
U23, U63: 74HC74; DIP-14_W7.62mm_LongPads
U24, U64: 74HC04; DIP-14_W7.62mm_LongPads
Y1: 6.144MHz; Crystal_HC49-U_Vertical

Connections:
BCLK: U4.9 (Q0), U8.3
CLK6M: U3.3, U4.10 (CLK)
CMP_L: R37.2, U21.7, U23.2 (D)
CMP_R: R77.2, U61.7, U63.2 (D)
DACN_L: R22.1, R29.1, U24.2
DACN_R: R62.1, R69.1, U64.2
DACP_L: R25.1, R34.1, U24.4
DACP_R: R65.1, R74.1, U64.4
DIN: U6.4 (Za), U8.11
GPCLK0: J1.3, J2.7
LRCLK: U4.4 (Q6), U8.7
MCLK: U4.7 (Q1), U6.1 (S), U23.3 (C), U63.3 (C)
unnamed: C16.1, R10.1, U9.1, Y1.1
unnamed: C17.1, R11.2, Y1.2
unnamed: C20.2, R20.1
unnamed: C21.1, R20.2, RV20.1
unnamed: C22.2, R24.1, U20.1
unnamed: C23.2, R28.1, U20.7
unnamed: C24.2, R31.1, R33.1, U22.1
unnamed: C60.2, R60.1
unnamed: C61.1, R60.2, RV60.1
unnamed: C62.2, R64.1, U60.1
unnamed: C63.2, R68.1, U60.7
unnamed: C64.2, R71.1, R73.1, U62.1
unnamed: C4.2, D1.2 (A), D2.1 (K)
unnamed: C5.2, D2.2 (A), R1.1
unnamed: J1.1, U9.4
unnamed: J1.2, U3.1, U3.2
unnamed: FB1.1, J2.2, J2.4
unnamed: C20.1, J20.1
unnamed: C60.1, J60.1
unnamed: R10.2, R11.1, U9.2, U9.3
unnamed: R12.1, U8.4
unnamed: R13.1, U8.10
unnamed: R21.1, RV20.2
unnamed: R27.1, R32.2, U22.7
unnamed: R61.1, RV60.2
unnamed: R67.1, R72.2, U62.7
unnamed: C4.1, U1.3 (2Y0), U1.5 (2Y1), U1.7 (2Y2), U1.9 (2Y3), U1.12 (1Y3), U1.14 (1Y2), U1.16 (1Y1), U1.18 (1Y0)
unnamed: R2.2, R3.1, U2.3 (+)
unnamed: R4.2, R5.1, U2.6 (-)
unnamed: U8.2, U8.5
unnamed: U8.6, U8.9
unnamed: U8.12, U8.14
unnamed: C22.1, R21.2, R22.2, R23.2, U20.2 (-)
unnamed: C23.1, R24.2, R25.2, R26.2, R27.2, U20.6 (-)
unnamed: R33.2, R34.2, R35.2, R36.2, U21.3 (-)
unnamed: C24.1, R28.2, R29.2, R30.2, U22.2 (-)
unnamed: R31.2, R32.1, U22.6 (-)
unnamed: C62.1, R61.2, R62.2, R63.2, U60.2 (-)
unnamed: C63.1, R64.2, R65.2, R66.2, R67.2, U60.6 (-)
unnamed: R73.2, R74.2, R75.2, R76.2, U61.3 (-)
unnamed: C64.1, R68.2, R69.2, R70.2, U62.2 (-)
unnamed: R71.2, R72.1, U62.6 (-)
PI_BCLK: J2.12, R12.2
PI_DIN: J2.38, U8.15
PI_LRCLK: J2.35, R13.2
PUMP: U1.2 (1A0), U1.4 (1A1), U1.6 (1A2), U1.8 (1A3), U1.11 (2A3), U1.13 (2A2), U1.15 (2A1), U1.17 (2A0), U4.3 (Q4)
QL: U6.3 (I1a), U23.5 (Q), U24.1
QNL: U23.6 (~Q), U24.3
QNR: U63.6 (~Q), U64.3
QR: U6.2 (I0a), U63.5 (Q), U64.1
VREF_N: R5.2, R23.1, R26.1, R30.1, R63.1, R66.1, R70.1, U2.7
VREF_P: R4.1, R35.1, R75.1, U2.1, U2.2 (-), U21.2 (+), U61.2 (+)

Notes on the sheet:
8 buffers paralleled ~= 32 mA;
so residual ripple lands on a CIC decimator null.
2u2 + 47k -> 1.5 Hz HP; 1k + 1n5 -> 106 kHz anti-alias.
QUANTISER (LM311 + retiming D-FF)
DACN = /Q, DACP = Q (taken from Q and /Q so the
REFERENCE (+/-2.5V, ratiometric -- tracks +5V so rail noise cancels as gain, not additive noise)
E LM311 quantiser on a single supply
B the +/-2.5 V ratiometric reference
192 kHz pump drive = 4x the 48 kHz output rate,
SPICE TESTBENCHES (sim/, one project each -- click to open)
INTEGRATOR 3 (a3 = 0.611)
two edges are as close to simultaneous as the parts allow)
R36 = R33 is what centres the threshold on VREF_P.
RESONATOR INVERTER (g = 0.0297)
no charge-pump IC in the shop
POWER (Pi +5V -> charge-pump -5V -> +/-2.5V DAC reference)
Q0=BCLK 3.072M Q1=MCLK 1.536M
INTEGRATOR 2 (a2 = 0.321, + resonator)
Jumper 1-2 = crystal Pierce (ps jitter -> ~100 dB floor).
CHANNEL R - 3rd-order CT delta-sigma, fs 1.536 MHz, OSR 32
1-BIT DAC DRIVE
INTEGRATOR 1 (a1 = 0.247)
CHANNEL L - 3rd-order CT delta-sigma, fs 1.536 MHz, OSR 32
For a quieter source drop R61: FS = 2.5 V x R61/R62.
F the 1-bit DAC and its offset leg
MCLK selects: DIN carries R,L,R,L... at 3.072 Mbps.
per signal so BCLK polarity is preserved -- inverting BCLK would
64 BCLK per LRCLK frame = 32 L bits + 32 R bits
Q4=PUMP 192k Q6=LRCLK 48k
attenuates from there. Overload is 0.70 FS = 1.7 Vrms in.
Pi is I2S SLAVE: this board is the clock master.
CLOCK AND DIGITAL (6.144 MHz -> /2 BCLK 3.072M, /4 MCLK 1.536M, /128 LRCLK 48k; L and R interleaved onto one DIN)
H one complete channel, with the click test
IMPEDANCE, not filtered by a series R.
spare gates: inputs tied low
Jumper 2-3 = Pi GPCLK0: ~1 ns -> 68 dB floor, the dominant
For a quieter source drop R21: FS = 2.5 V x R21/R22.
R34 is the excess-loop-delay compensation: without it the
= exactly one OSR-32 sample per channel.
R74 is the excess-loop-delay compensation: without it the

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
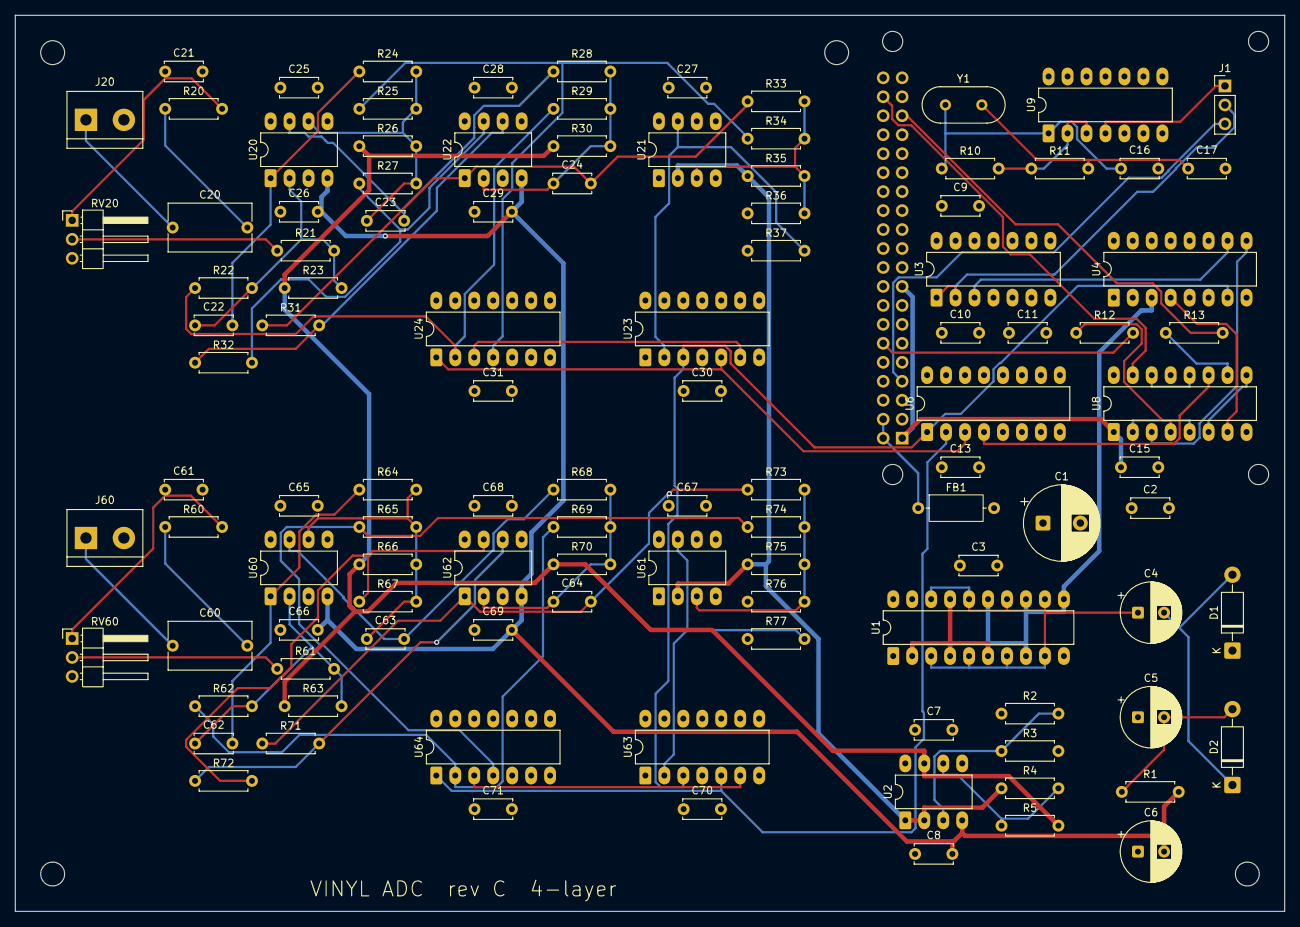
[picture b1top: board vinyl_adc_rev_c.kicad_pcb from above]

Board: 4 copper layers, 170.0 x 120.0 mm, 119 parts (1 on the bottom side), 68 nets.

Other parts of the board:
H1, H2, H3, H4: MountingHole_3.2mm_M3
H5, H6, H7, H8: MountingHole_2.7mm_M2.5

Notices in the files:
README.md:
License:
MIT License — free for personal and educational use.
License: MIT
